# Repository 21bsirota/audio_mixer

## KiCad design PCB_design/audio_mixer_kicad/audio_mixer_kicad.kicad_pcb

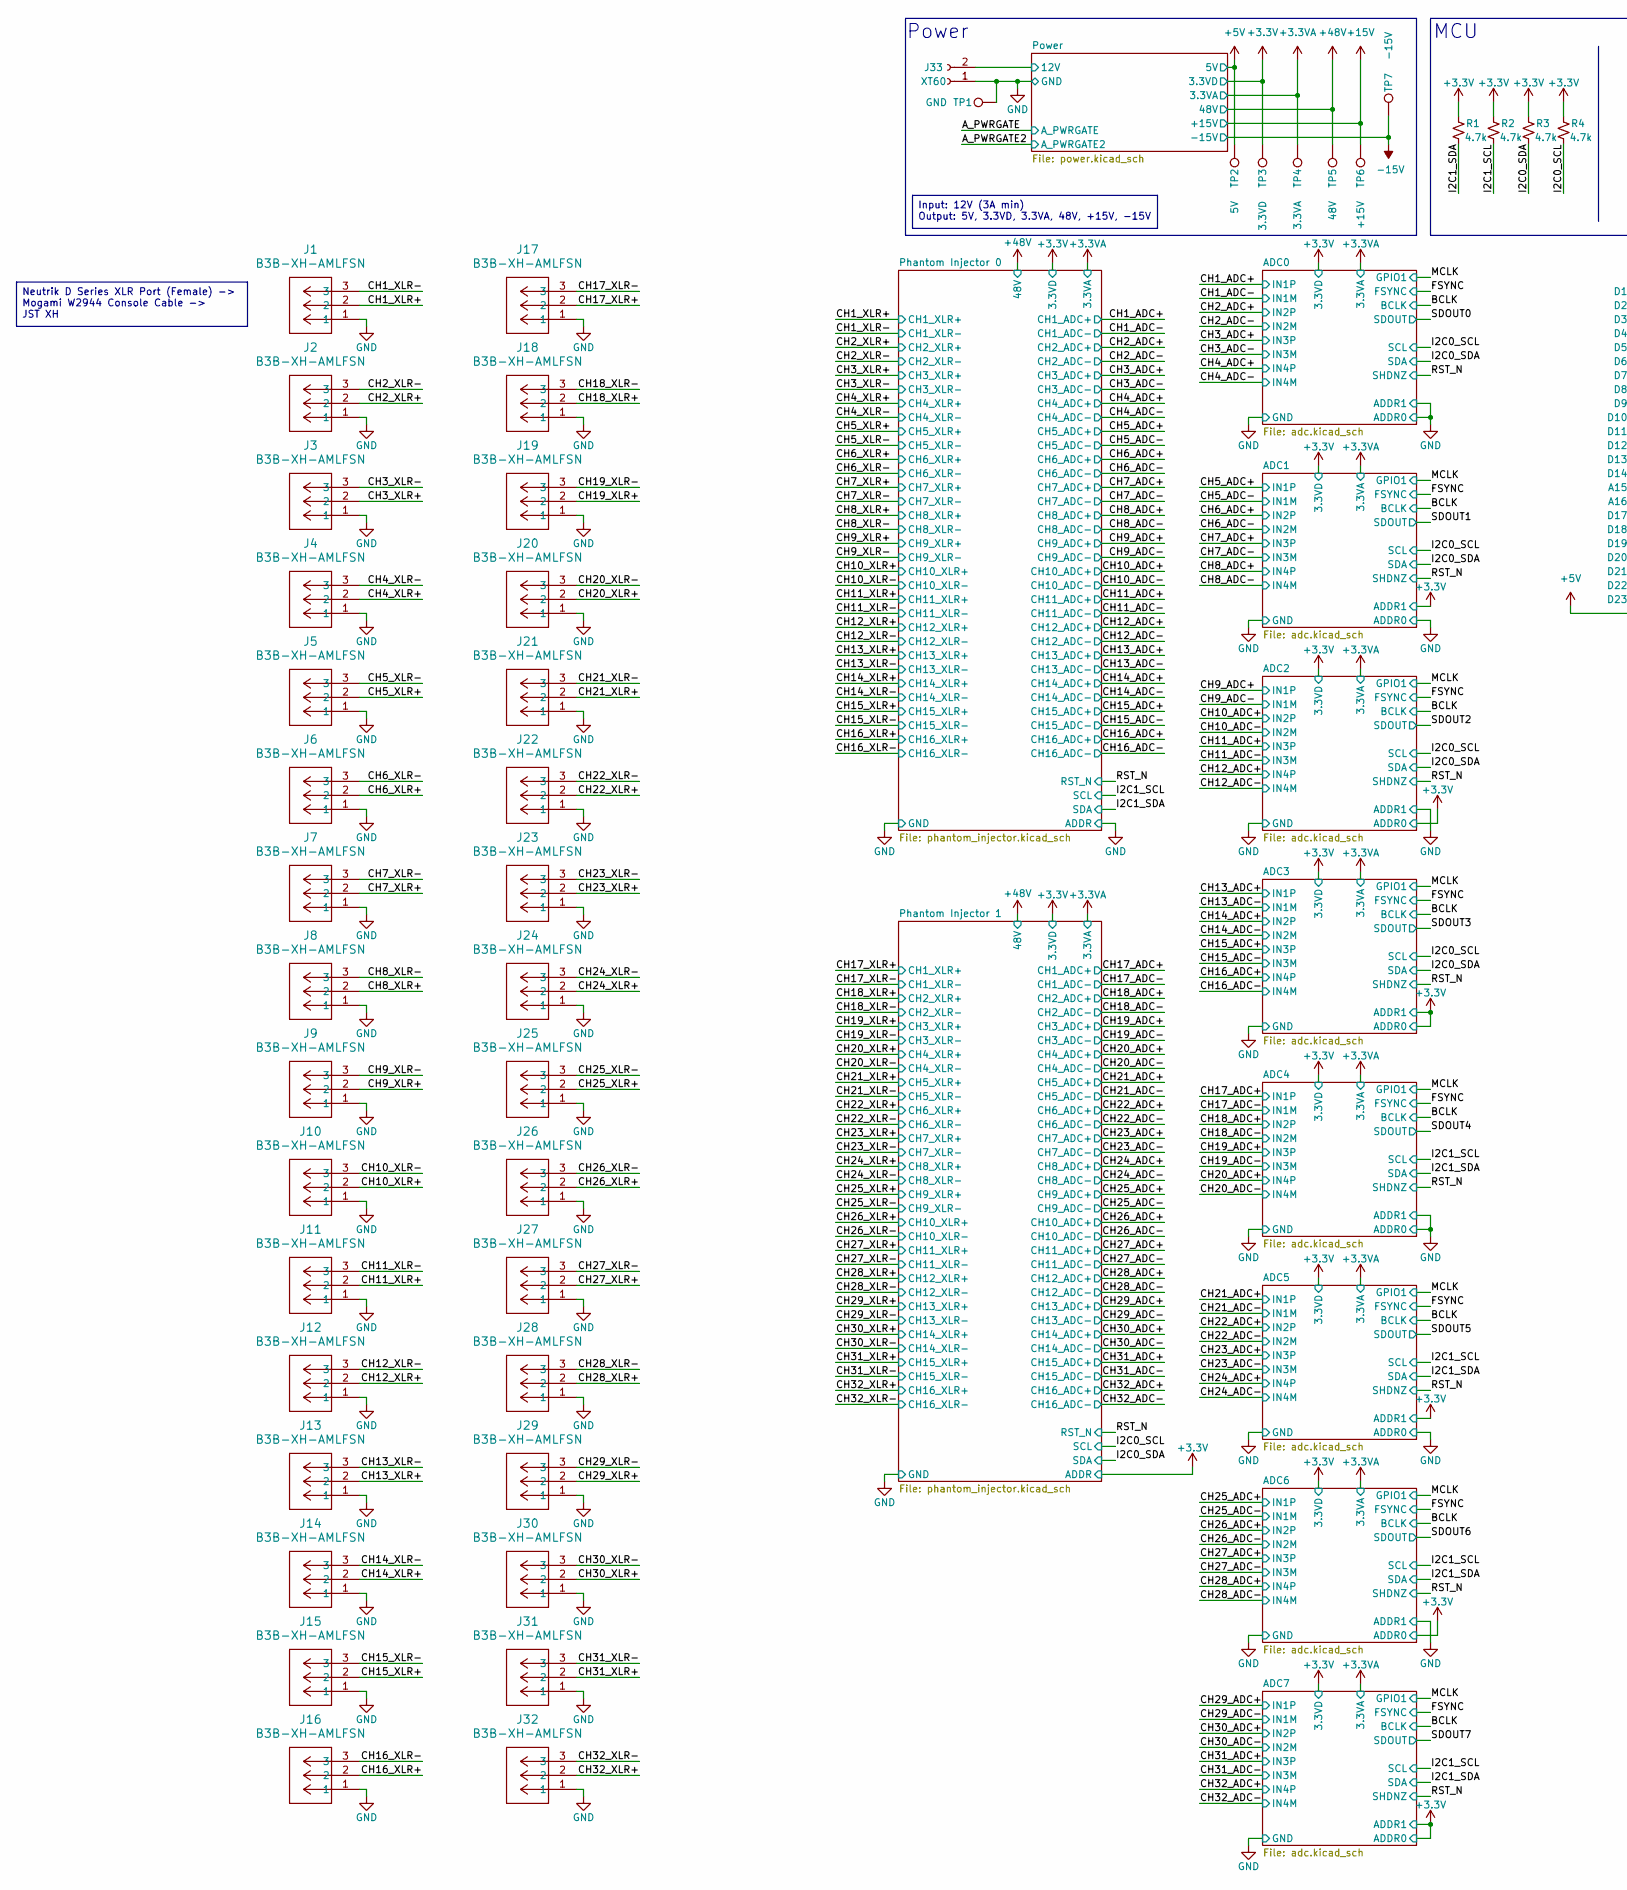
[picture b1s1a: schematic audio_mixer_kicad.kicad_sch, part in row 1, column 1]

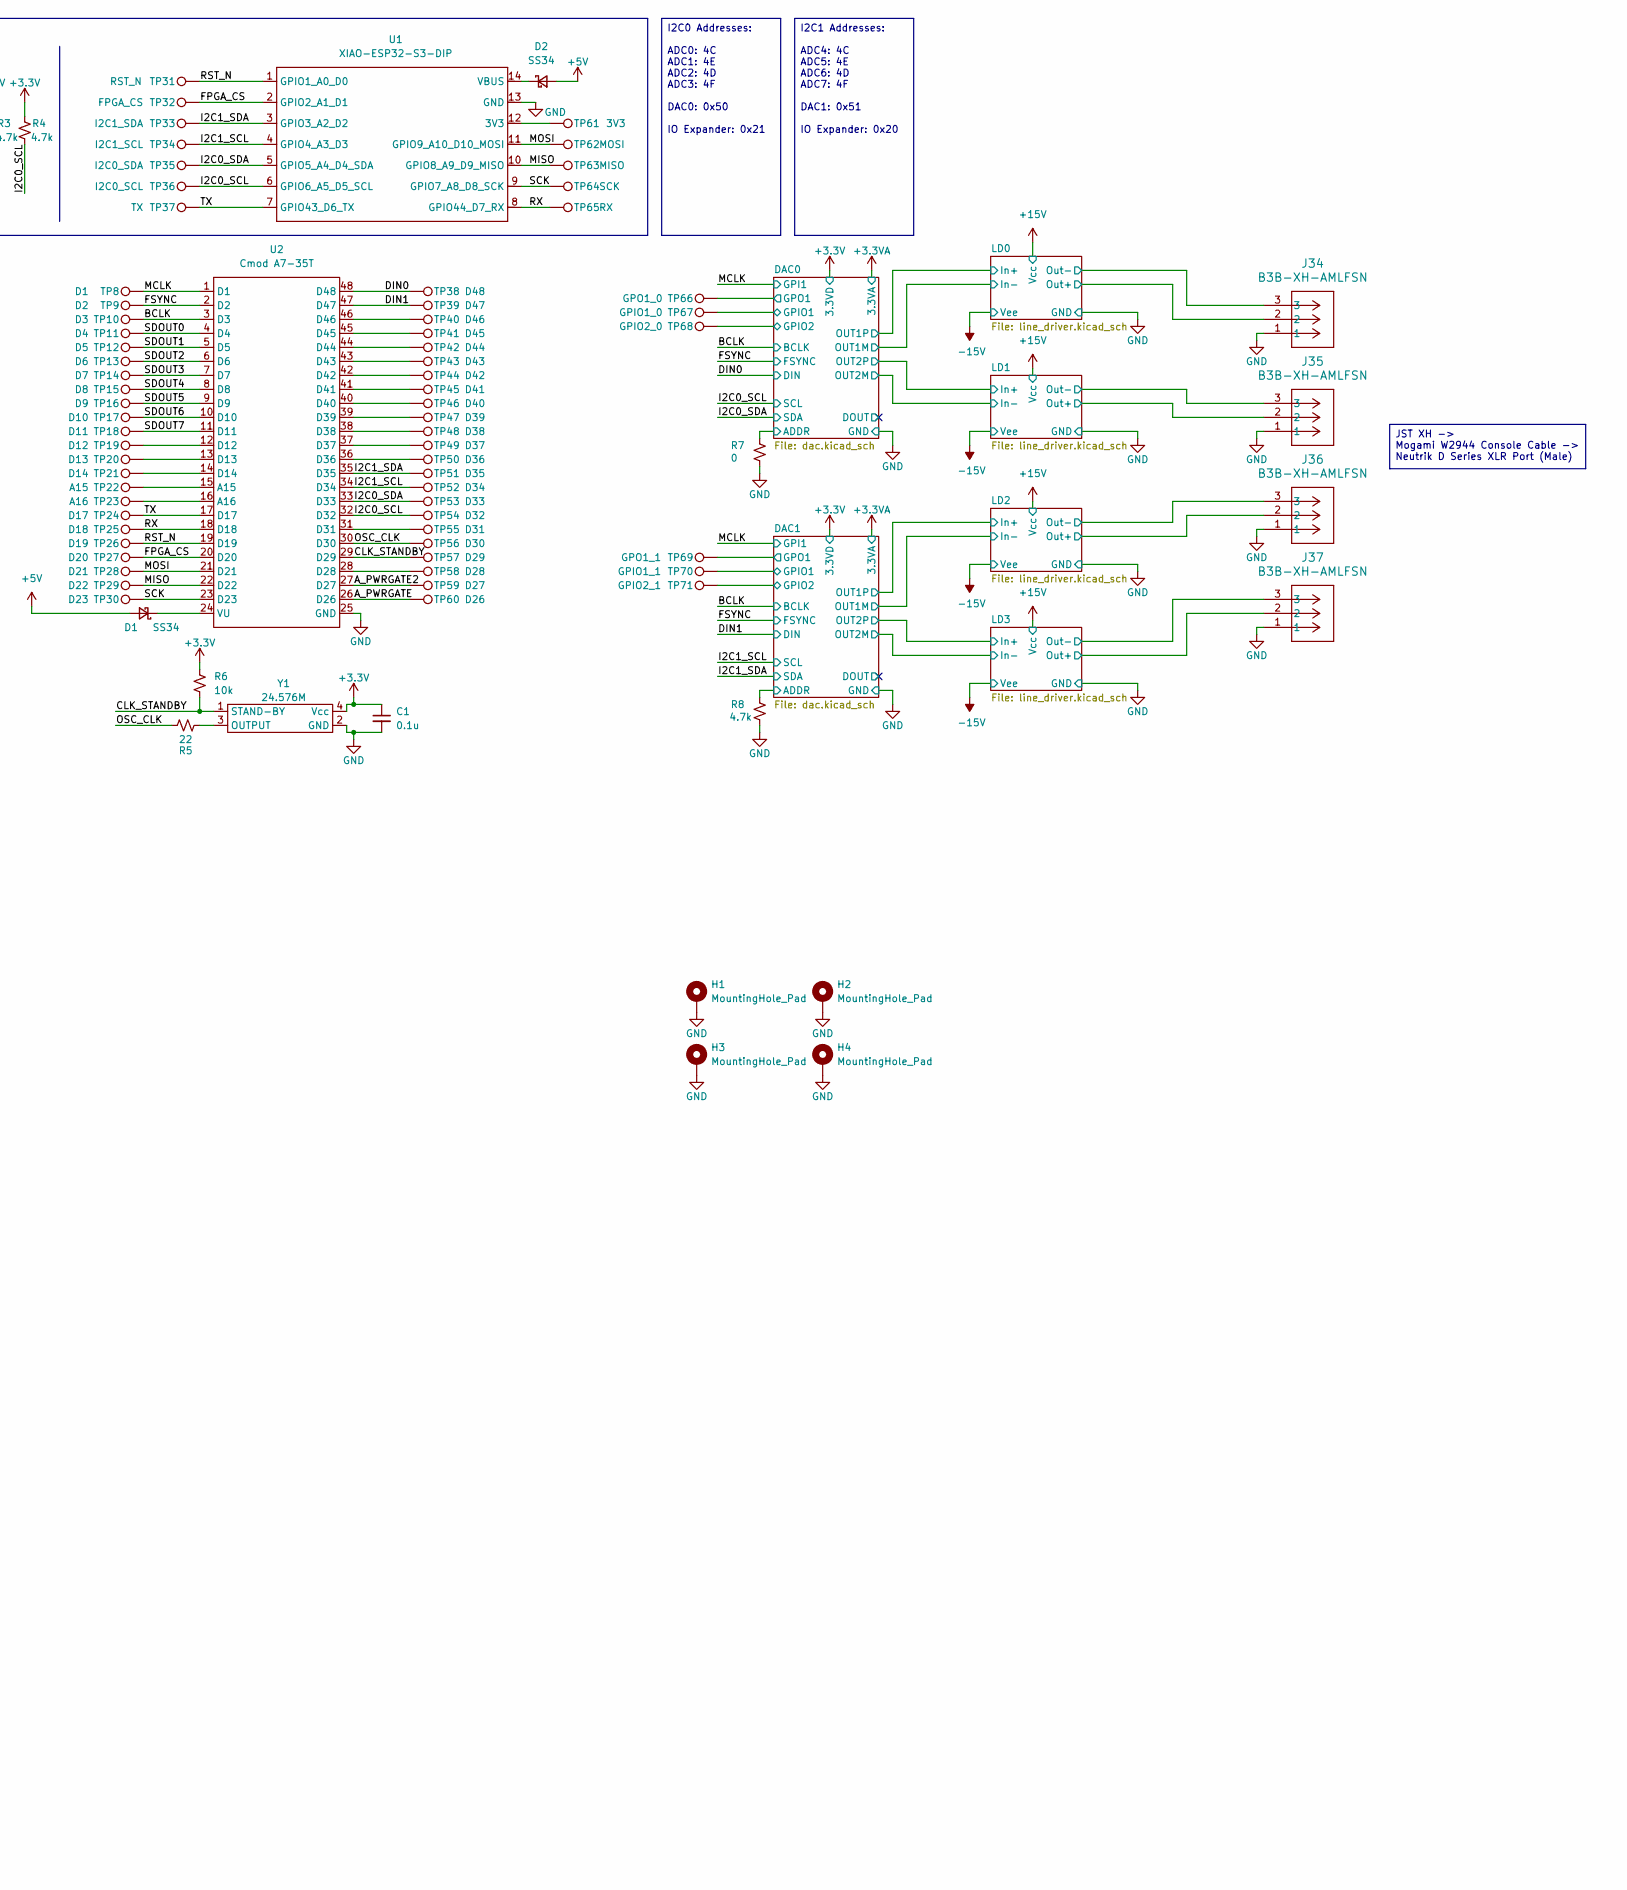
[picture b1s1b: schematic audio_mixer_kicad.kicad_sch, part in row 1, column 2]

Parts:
C1: 0.1u; C_1206_3216Metric_Pad1.33x1.80mm_HandSolder
D1, D2: SS34; DIOM7959X265N
H1, H2, H3, H4: MountingHole_Pad; MountingHole_3.2mm_M3_Pad_TopBottom
J1, J2, J3, J4, J5, J6, J7, J8, J9, J10, J11, J12, J13, J14, J15, J16, J17, J18, J19, J20, J21, J22, J23, J24, J25, J26, J27, J28, J29, J30, J31, J32, J34, J35, J36, J37: B3B-XH-AMLFSN; CONN_B3B-XH-AMLFSN_JST
J33: XT60; AMASS_XT60-M_1x02_P7.20mm_Vertical
R1, R2, R3, R4, R8: 4.7k; R_1206_3216Metric_Pad1.30x1.75mm_HandSolder
R5: 22; R_1206_3216Metric_Pad1.30x1.75mm_HandSolder
R6: 10k; R_1206_3216Metric_Pad1.30x1.75mm_HandSolder
R7: 0; R_1206_3216Metric_Pad1.30x1.75mm_HandSolder
TP1: GND; TestPoint_THTPad_D2.0mm_Drill1.0mm
TP2: 5V; TestPoint_THTPad_D2.0mm_Drill1.0mm
TP3: 3.3VD; TestPoint_THTPad_D2.0mm_Drill1.0mm
TP4: 3.3VA; TestPoint_THTPad_D2.0mm_Drill1.0mm
TP5: 48V; TestPoint_THTPad_D2.0mm_Drill1.0mm
TP6: +15V; TestPoint_THTPad_D2.0mm_Drill1.0mm
TP7: -15V; TestPoint_THTPad_D2.0mm_Drill1.0mm
TP8: D1; TestPoint_THTPad_D2.0mm_Drill1.0mm
TP9: D2; TestPoint_THTPad_D2.0mm_Drill1.0mm
TP10: D3; TestPoint_THTPad_D2.0mm_Drill1.0mm
TP11: D4; TestPoint_THTPad_D2.0mm_Drill1.0mm
TP12: D5; TestPoint_THTPad_D2.0mm_Drill1.0mm
TP13: D6; TestPoint_THTPad_D2.0mm_Drill1.0mm
TP14: D7; TestPoint_THTPad_D2.0mm_Drill1.0mm
TP15: D8; TestPoint_THTPad_D2.0mm_Drill1.0mm
TP16: D9; TestPoint_THTPad_D2.0mm_Drill1.0mm
TP17: D10; TestPoint_THTPad_D2.0mm_Drill1.0mm
TP18: D11; TestPoint_THTPad_D2.0mm_Drill1.0mm
TP19: D12; TestPoint_THTPad_D2.0mm_Drill1.0mm
TP20: D13; TestPoint_THTPad_D2.0mm_Drill1.0mm
TP21: D14; TestPoint_THTPad_D2.0mm_Drill1.0mm
TP22: A15; TestPoint_THTPad_D2.0mm_Drill1.0mm
TP23: A16; TestPoint_THTPad_D2.0mm_Drill1.0mm
TP24: D17; TestPoint_THTPad_D2.0mm_Drill1.0mm
TP25: D18; TestPoint_THTPad_D2.0mm_Drill1.0mm
TP26: D19; TestPoint_THTPad_D2.0mm_Drill1.0mm
TP27: D20; TestPoint_THTPad_D2.0mm_Drill1.0mm
TP28: D21; TestPoint_THTPad_D2.0mm_Drill1.0mm
TP29: D22; TestPoint_THTPad_D2.0mm_Drill1.0mm
TP30: D23; TestPoint_THTPad_D2.0mm_Drill1.0mm
TP31: RST_N; TestPoint_THTPad_D2.0mm_Drill1.0mm
TP32: FPGA_CS; TestPoint_THTPad_D2.0mm_Drill1.0mm
TP33: I2C1_SDA; TestPoint_THTPad_D2.0mm_Drill1.0mm
TP34: I2C1_SCL; TestPoint_THTPad_D2.0mm_Drill1.0mm
TP35: I2C0_SDA; TestPoint_THTPad_D2.0mm_Drill1.0mm
TP36: I2C0_SCL; TestPoint_THTPad_D2.0mm_Drill1.0mm
TP37: TX; TestPoint_THTPad_D2.0mm_Drill1.0mm
TP38: D48; TestPoint_THTPad_D2.0mm_Drill1.0mm
TP39: D47; TestPoint_THTPad_D2.0mm_Drill1.0mm
TP40: D46; TestPoint_THTPad_D2.0mm_Drill1.0mm
TP41: D45; TestPoint_THTPad_D2.0mm_Drill1.0mm
TP42: D44; TestPoint_THTPad_D2.0mm_Drill1.0mm
TP43: D43; TestPoint_THTPad_D2.0mm_Drill1.0mm
TP44: D42; TestPoint_THTPad_D2.0mm_Drill1.0mm
TP45: D41; TestPoint_THTPad_D2.0mm_Drill1.0mm
TP46: D40; TestPoint_THTPad_D2.0mm_Drill1.0mm
TP47: D39; TestPoint_THTPad_D2.0mm_Drill1.0mm
TP48: D38; TestPoint_THTPad_D2.0mm_Drill1.0mm
TP49: D37; TestPoint_THTPad_D2.0mm_Drill1.0mm
TP50: D36; TestPoint_THTPad_D2.0mm_Drill1.0mm
TP51: D35; TestPoint_THTPad_D2.0mm_Drill1.0mm
TP52: D34; TestPoint_THTPad_D2.0mm_Drill1.0mm
TP53: D33; TestPoint_THTPad_D2.0mm_Drill1.0mm
TP54: D32; TestPoint_THTPad_D2.0mm_Drill1.0mm
TP55: D31; TestPoint_THTPad_D2.0mm_Drill1.0mm
TP56: D30; TestPoint_THTPad_D2.0mm_Drill1.0mm
TP57: D29; TestPoint_THTPad_D2.0mm_Drill1.0mm
TP58: D28; TestPoint_THTPad_D2.0mm_Drill1.0mm
TP59: D27; TestPoint_THTPad_D2.0mm_Drill1.0mm
TP60: D26; TestPoint_THTPad_D2.0mm_Drill1.0mm
TP61: 3V3; TestPoint_THTPad_D2.0mm_Drill1.0mm
TP62: MOSI; TestPoint_THTPad_D2.0mm_Drill1.0mm
TP63: MISO; TestPoint_THTPad_D2.0mm_Drill1.0mm
TP64: SCK; TestPoint_THTPad_D2.0mm_Drill1.0mm
TP65: RX; TestPoint_THTPad_D2.0mm_Drill1.0mm
TP66: GPO1_0; TestPoint_THTPad_D2.0mm_Drill1.0mm
TP67: GPIO1_0; TestPoint_THTPad_D2.0mm_Drill1.0mm
TP68: GPIO2_0; TestPoint_THTPad_D2.0mm_Drill1.0mm
TP69: GPO1_1; TestPoint_THTPad_D2.0mm_Drill1.0mm
TP70: GPIO1_1; TestPoint_THTPad_D2.0mm_Drill1.0mm
TP71: GPIO2_1; TestPoint_THTPad_D2.0mm_Drill1.0mm
U1: XIAO-ESP32-S3-DIP
U2: Cmod A7-35T; Cmod-A7
Y1: 24.576M; NZ2520SDA

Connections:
+3.3V: C1.1, R1.1, R2.1, R3.1, R4.1, R6.1, TP3.1 (1_1), Y1.4 (Vcc); also elsewhere on the board
+3.3VA: TP4.1 (1_1); also elsewhere on the board
+5V: D1.2 (A), D2.2 (A), TP2.1 (1_1); also elsewhere on the board
+12V: J33.2; also elsewhere on the board
+15V: TP6.1 (1_1); also elsewhere on the board
+48V: TP5.1 (1_1); also elsewhere on the board
-15V: TP7.1 (1_1); also elsewhere on the board
/A_PWRGATE: TP60.1 (1_1), U2.26 (D26); also elsewhere on the board
/A_PWRGATE2: TP59.1 (1_1), U2.27 (D27); also elsewhere on the board
/BCLK: TP10.1 (1_1), U2.3 (D3); also elsewhere on the board
/CH1_XLR+: J1.2; also elsewhere on the board
/CH1_XLR-: J1.3; also elsewhere on the board
/CH2_XLR+: J2.2; also elsewhere on the board
/CH2_XLR-: J2.3; also elsewhere on the board
/CH3_XLR+: J3.2; also elsewhere on the board
/CH3_XLR-: J3.3; also elsewhere on the board
/CH4_XLR+: J4.2; also elsewhere on the board
/CH4_XLR-: J4.3; also elsewhere on the board
/CH5_XLR+: J5.2; also elsewhere on the board
/CH5_XLR-: J5.3; also elsewhere on the board
/CH6_XLR+: J6.2; also elsewhere on the board
/CH6_XLR-: J6.3; also elsewhere on the board
/CH7_XLR+: J7.2; also elsewhere on the board
/CH7_XLR-: J7.3; also elsewhere on the board
/CH8_XLR+: J8.2; also elsewhere on the board
/CH8_XLR-: J8.3; also elsewhere on the board
/CH9_XLR+: J9.2; also elsewhere on the board
/CH9_XLR-: J9.3; also elsewhere on the board
/CH10_XLR+: J10.2; also elsewhere on the board
/CH10_XLR-: J10.3; also elsewhere on the board
/CH11_XLR+: J11.2; also elsewhere on the board
/CH11_XLR-: J11.3; also elsewhere on the board
/CH12_XLR+: J12.2; also elsewhere on the board
/CH12_XLR-: J12.3; also elsewhere on the board
/CH13_XLR+: J13.2; also elsewhere on the board
/CH13_XLR-: J13.3; also elsewhere on the board
/CH14_XLR+: J14.2; also elsewhere on the board
/CH14_XLR-: J14.3; also elsewhere on the board
/CH15_XLR+: J15.2; also elsewhere on the board
/CH15_XLR-: J15.3; also elsewhere on the board
/CH16_XLR+: J16.2; also elsewhere on the board
/CH16_XLR-: J16.3; also elsewhere on the board
/CH17_XLR+: J17.2; also elsewhere on the board
/CH17_XLR-: J17.3; also elsewhere on the board
/CH18_XLR+: J18.2; also elsewhere on the board
/CH18_XLR-: J18.3; also elsewhere on the board
/CH19_XLR+: J19.2; also elsewhere on the board
/CH19_XLR-: J19.3; also elsewhere on the board
/CH20_XLR+: J20.2; also elsewhere on the board
/CH20_XLR-: J20.3; also elsewhere on the board
/CH21_XLR+: J21.2; also elsewhere on the board
/CH21_XLR-: J21.3; also elsewhere on the board
/CH22_XLR+: J22.2; also elsewhere on the board
/CH22_XLR-: J22.3; also elsewhere on the board
/CH23_XLR+: J23.2; also elsewhere on the board
/CH23_XLR-: J23.3; also elsewhere on the board
/CH24_XLR+: J24.2; also elsewhere on the board
/CH24_XLR-: J24.3; also elsewhere on the board
/CH25_XLR+: J25.2; also elsewhere on the board
/CH25_XLR-: J25.3; also elsewhere on the board
/CH26_XLR+: J26.2; also elsewhere on the board
/CH26_XLR-: J26.3; also elsewhere on the board
/CH27_XLR+: J27.2; also elsewhere on the board
/CH27_XLR-: J27.3; also elsewhere on the board
/CH28_XLR+: J28.2; also elsewhere on the board
/CH28_XLR-: J28.3; also elsewhere on the board
/CH29_XLR+: J29.2; also elsewhere on the board
/CH29_XLR-: J29.3; also elsewhere on the board
/CH30_XLR+: J30.2; also elsewhere on the board
/CH30_XLR-: J30.3; also elsewhere on the board
/CH31_XLR+: J31.2; also elsewhere on the board
/CH31_XLR-: J31.3; also elsewhere on the board
/CH32_XLR+: J32.2; also elsewhere on the board
/CH32_XLR-: J32.3; also elsewhere on the board
/CLK_STANDBY: R6.2, TP57.1 (1_1), U2.29 (D29), Y1.1 (STAND-BY)
/DAC0/ADDR: R7.1; also elsewhere on the board
/DAC0/GPIO1: TP67.1 (1_1); also elsewhere on the board
/DAC0/GPIO2: TP68.1 (1_1); also elsewhere on the board
/DAC0/GPO1: TP66.1 (1_1); also elsewhere on the board
/DAC1/ADDR: R8.1; also elsewhere on the board
/DAC1/GPIO1: TP70.1 (1_1); also elsewhere on the board
/DAC1/GPIO2: TP71.1 (1_1); also elsewhere on the board
/DAC1/GPO1: TP69.1 (1_1); also elsewhere on the board
/DIN0: TP38.1 (1_1), U2.48 (D48); also elsewhere on the board
/DIN1: TP39.1 (1_1), U2.47 (D47); also elsewhere on the board
/FPGA_CS: TP27.1 (1_1), TP32.1 (1_1), U1.2 (GPIO2_A1_D1), U2.20 (D20)
/FSYNC: TP9.1 (1_1), U2.2 (D2); also elsewhere on the board
/I2C0_SCL: R4.2, TP36.1 (1_1), TP54.1 (1_1), U1.6 (GPIO6_A5_D5_SCL), U2.32 (D32); also elsewhere on the board
/I2C0_SDA: R3.2, TP35.1 (1_1), TP53.1 (1_1), U1.5 (GPIO5_A4_D4_SDA), U2.33 (D33); also elsewhere on the board
/I2C1_SCL: R2.2, TP34.1 (1_1), TP52.1 (1_1), U1.4 (GPIO4_A3_D3), U2.34 (D34); also elsewhere on the board
/I2C1_SDA: R1.2, TP33.1 (1_1), TP51.1 (1_1), U1.3 (GPIO3_A2_D2), U2.35 (D35); also elsewhere on the board
/LD0/Out+: J34.2; also elsewhere on the board
/LD0/Out-: J34.3; also elsewhere on the board
/LD1/Out+: J35.2; also elsewhere on the board
/LD1/Out-: J35.3; also elsewhere on the board
/LD2/Out+: J36.2; also elsewhere on the board
/LD2/Out-: J36.3; also elsewhere on the board
/LD3/Out+: J37.2; also elsewhere on the board
/LD3/Out-: J37.3; also elsewhere on the board
/MCLK: TP8.1 (1_1), U2.1 (D1); also elsewhere on the board
/MISO: TP29.1 (1_1), TP63.1 (1_1), U1.10 (GPIO8_A9_D9_MISO), U2.22 (D22)
/MOSI: TP28.1 (1_1), TP62.1 (1_1), U1.11 (GPIO9_A10_D10_MOSI), U2.21 (D21)
/OSC_CLK: R5.1, TP56.1 (1_1), U2.30 (D30)
/RST_N: TP26.1 (1_1), TP31.1 (1_1), U1.1 (GPIO1_A0_D0), U2.19 (D19); also elsewhere on the board
/RX: TP25.1 (1_1), TP65.1 (1_1), U1.8 (GPIO44_D7_RX), U2.18 (D18)
/SCK: TP30.1 (1_1), TP64.1 (1_1), U1.9 (GPIO7_A8_D8_SCK), U2.23 (D23)
/SDOUT0: TP11.1 (1_1), U2.4 (D4); also elsewhere on the board
/SDOUT1: TP12.1 (1_1), U2.5 (D5); also elsewhere on the board
/SDOUT2: TP13.1 (1_1), U2.6 (D6); also elsewhere on the board
/SDOUT3: TP14.1 (1_1), U2.7 (D7); also elsewhere on the board
/SDOUT4: TP15.1 (1_1), U2.8 (D8); also elsewhere on the board
/SDOUT5: TP16.1 (1_1), U2.9 (D9); also elsewhere on the board
/SDOUT6: TP17.1 (1_1), U2.10 (D10); also elsewhere on the board
/SDOUT7: TP18.1 (1_1), U2.11 (D11); also elsewhere on the board
/TX: TP24.1 (1_1), TP37.1 (1_1), U1.7 (GPIO43_D6_TX), U2.17 (D17)
GND: C1.2, H1.1 (1_1), H2.1 (1_1), H3.1 (1_1), H4.1 (1_1), J1.1, J2.1, J3.1, J4.1, J5.1, J6.1, J7.1, J8.1, J9.1, J10.1, J11.1, J12.1, J13.1, J14.1, J15.1, J16.1, J17.1, J18.1, J19.1, J20.1, J21.1, J22.1, J23.1, J24.1, J25.1, J26.1, J27.1, J28.1, J29.1, J30.1, J31.1, J32.1, J33.1, J34.1, J35.1, J36.1, J37.1, R7.2, R8.2, TP1.1 (1_1), U1.13 (GND), U2.25 (GND), Y1.2 (GND); also elsewhere on the board
unnamed: D1.1 (K), U2.24 (VU)
unnamed: D2.1 (K), U1.14 (VBUS)
unnamed: TP61.1 (1_1), U1.12 (3V3)
unnamed: TP22.1 (1_1), U2.15 (A15)
unnamed: TP23.1 (1_1), U2.16 (A16)
unnamed: TP19.1 (1_1), U2.12 (D12)
unnamed: TP20.1 (1_1), U2.13 (D13)
unnamed: TP21.1 (1_1), U2.14 (D14)
unnamed: TP58.1 (1_1), U2.28 (D28)
unnamed: TP55.1 (1_1), U2.31 (D31)
unnamed: TP50.1 (1_1), U2.36 (D36)
unnamed: TP49.1 (1_1), U2.37 (D37)
unnamed: TP48.1 (1_1), U2.38 (D38)
unnamed: TP47.1 (1_1), U2.39 (D39)
unnamed: TP46.1 (1_1), U2.40 (D40)
unnamed: TP45.1 (1_1), U2.41 (D41)
unnamed: TP44.1 (1_1), U2.42 (D42)
unnamed: TP43.1 (1_1), U2.43 (D43)
unnamed: TP42.1 (1_1), U2.44 (D44)
unnamed: TP41.1 (1_1), U2.45 (D45)
unnamed: TP40.1 (1_1), U2.46 (D46)
unnamed: R5.2, Y1.3 (OUTPUT)

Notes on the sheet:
MCU
Power
JST XH -> Mogami W2944 Console Cable -> Neutrik D Series XLR Port (Male)
Neutrik D Series XLR Port (Female) -> Mogami W2944 Console Cable -> JST XH
I2C1 Addresses: ADC4: 4C ADC5: 4E ADC6: 4D ADC7: 4F DAC1: 0x51 IO Expander: 0x20
I2C0 Addresses: ADC0: 4C ADC1: 4E ADC2: 4D ADC3: 4F DAC0: 0x50 IO Expander: 0x21
Input: 12V (3A min) Output: 5V, 3.3VD, 3.3VA, 48V, +15V, -15V

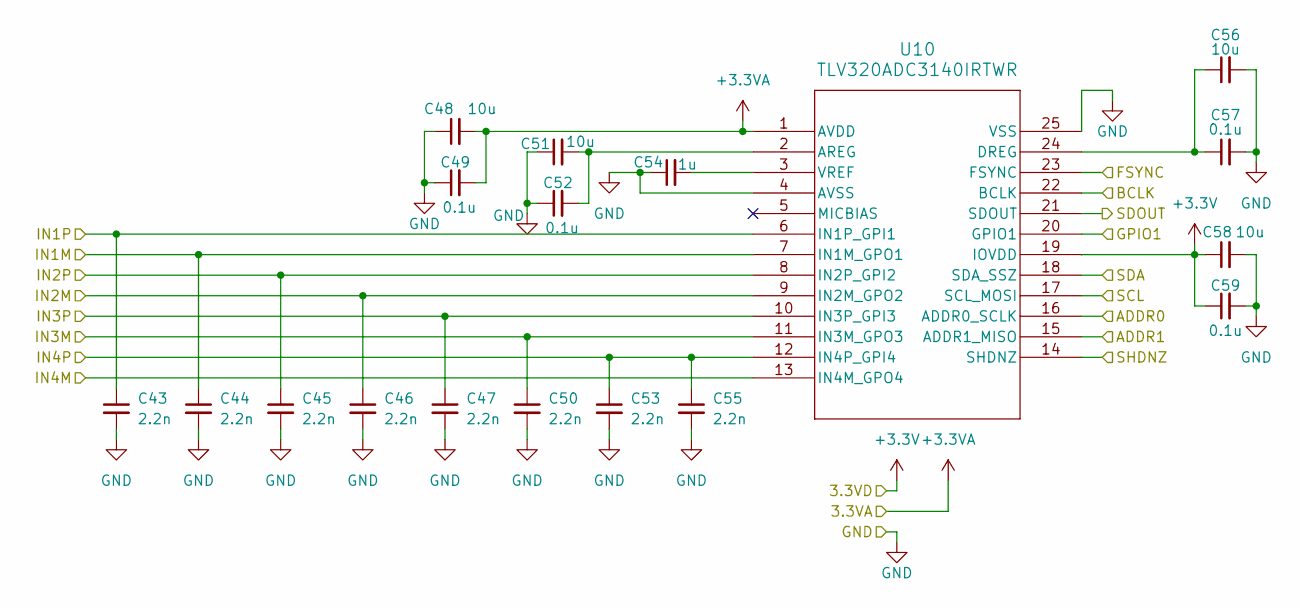
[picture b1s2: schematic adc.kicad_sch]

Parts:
C43, C44, C45, C46, C47, C50, C53, C55: 2.2n; C_1206_3216Metric_Pad1.33x1.80mm_HandSolder
C48, C51, C56, C58: 10u; C_1206_3216Metric_Pad1.33x1.80mm_HandSolder
C49, C52, C57, C59: 0.1u; C_1206_3216Metric_Pad1.33x1.80mm_HandSolder
C54: 1u; C_1206_3216Metric_Pad1.33x1.80mm_HandSolder
U10: TLV320ADC3140IRTWR; TLV320ADC3140IRTWR_TEX

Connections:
+3.3V: C58.1, C59.1, U10.19 (IOVDD); also elsewhere on the board
+3.3VA: C48.2, C49.2, U10.1 (AVDD); also elsewhere on the board
/BCLK: U10.22 (BCLK); also elsewhere on the board
/CH1_ADC+: C43.1, U10.6 (IN1P_GPI1); also elsewhere on the board
/CH1_ADC-: C44.1, U10.7 (IN1M_GPO1); also elsewhere on the board
/CH2_ADC+: C45.1, U10.8 (IN2P_GPI2); also elsewhere on the board
/CH2_ADC-: C46.1, U10.9 (IN2M_GPO2); also elsewhere on the board
/CH3_ADC+: C47.1, U10.10 (IN3P_GPI3); also elsewhere on the board
/CH3_ADC-: C50.1, U10.11 (IN3M_GPO3); also elsewhere on the board
/CH4_ADC+: C53.1, C55.1, U10.12 (IN4P_GPI4); also elsewhere on the board
/CH4_ADC-: U10.13 (IN4M_GPO4); also elsewhere on the board
/FSYNC: U10.23 (FSYNC); also elsewhere on the board
/I2C0_SCL: U10.17 (SCL_MOSI); also elsewhere on the board
/I2C0_SDA: U10.18 (SDA_SSZ); also elsewhere on the board
/MCLK: U10.20 (GPIO1); also elsewhere on the board
/RST_N: U10.14 (SHDNZ); also elsewhere on the board
/SDOUT0: U10.21 (SDOUT); also elsewhere on the board
GND: C43.2, C44.2, C45.2, C46.2, C47.2, C48.1, C49.1, C50.2, C51.1, C52.1, C53.2, C54.1, C55.2, C56.2, C57.2, C58.2, C59.2, U10.4 (AVSS), U10.15 (ADDR1_MISO), U10.16 (ADDR0_SCLK), U10.25 (VSS); also elsewhere on the board
unnamed: C51.2, C52.2, U10.2 (AREG)
unnamed: C56.1, C57.1, U10.24 (DREG)
unnamed: C54.2, U10.3 (VREF)

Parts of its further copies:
C60, C61, C62, C63, C64, C67, C70, C72, C77, C78, C79, C80, C81, C84, C87, C89, C94, C95, C96, C97, C98, C101, C104, C106, C111, C112, C113, C114, C115, C118, C121, C123, C128, C129, C130, C131, C132, C135, C138, C140, C145, C146, C147, C148, C149, C152, C155, C157, C162, C163, C164, C165, C166, C169, C172, C174: 2.2n; C_1206_3216Metric_Pad1.33x1.80mm_HandSolder
C65, C68, C73, C75, C82, C85, C90, C92, C99, C102, C107, C109, C116, C119, C124, C126, C133, C136, C141, C143, C150, C153, C158, C160, C167, C170, C175, C177: 10u; C_1206_3216Metric_Pad1.33x1.80mm_HandSolder
C66, C69, C74, C76, C83, C86, C91, C93, C100, C103, C108, C110, C117, C120, C125, C127, C134, C137, C142, C144, C151, C154, C159, C161, C168, C171, C176, C178: 0.1u; C_1206_3216Metric_Pad1.33x1.80mm_HandSolder
C71, C88, C105, C122, C139, C156, C173: 1u; C_1206_3216Metric_Pad1.33x1.80mm_HandSolder
U11, U12, U13, U14, U15, U16, U17: TLV320ADC3140IRTWR; TLV320ADC3140IRTWR_TEX

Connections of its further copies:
+3.3V: C75.1, C76.1, C92.1, C93.1, C109.1, C110.1, C126.1, C127.1, C143.1, C144.1, C160.1, C161.1, C177.1, C178.1, U11.15 (ADDR1_MISO), U11.19 (IOVDD), U12.16 (ADDR0_SCLK), U12.19 (IOVDD), U13.15 (ADDR1_MISO), U13.16 (ADDR0_SCLK), U13.19 (IOVDD), U14.19 (IOVDD), U15.15 (ADDR1_MISO), U15.19 (IOVDD), U16.16 (ADDR0_SCLK), U16.19 (IOVDD), U17.15 (ADDR1_MISO), U17.16 (ADDR0_SCLK), U17.19 (IOVDD); also elsewhere on the board
+3.3VA: C65.2, C66.2, C82.2, C83.2, C99.2, C100.2, C116.2, C117.2, C133.2, C134.2, C150.2, C151.2, C167.2, C168.2, U11.1 (AVDD), U12.1 (AVDD), U13.1 (AVDD), U14.1 (AVDD), U15.1 (AVDD), U16.1 (AVDD), U17.1 (AVDD); also elsewhere on the board
/BCLK: U11.22 (BCLK), U12.22 (BCLK), U13.22 (BCLK), U14.22 (BCLK), U15.22 (BCLK), U16.22 (BCLK), U17.22 (BCLK); also elsewhere on the board
/CH5_ADC+: C60.1, U11.6 (IN1P_GPI1); also elsewhere on the board
/CH5_ADC-: C61.1, U11.7 (IN1M_GPO1); also elsewhere on the board
/CH6_ADC+: C62.1, U11.8 (IN2P_GPI2); also elsewhere on the board
/CH6_ADC-: C63.1, U11.9 (IN2M_GPO2); also elsewhere on the board
/CH7_ADC+: C64.1, U11.10 (IN3P_GPI3); also elsewhere on the board
/CH7_ADC-: C67.1, U11.11 (IN3M_GPO3); also elsewhere on the board
/CH8_ADC+: C70.1, C72.1, U11.12 (IN4P_GPI4); also elsewhere on the board
/CH8_ADC-: U11.13 (IN4M_GPO4); also elsewhere on the board
/CH9_ADC+: C77.1, U12.6 (IN1P_GPI1); also elsewhere on the board
/CH9_ADC-: C78.1, U12.7 (IN1M_GPO1); also elsewhere on the board
/CH10_ADC+: C79.1, U12.8 (IN2P_GPI2); also elsewhere on the board
/CH10_ADC-: C80.1, U12.9 (IN2M_GPO2); also elsewhere on the board
/CH11_ADC+: C81.1, U12.10 (IN3P_GPI3); also elsewhere on the board
/CH11_ADC-: C84.1, U12.11 (IN3M_GPO3); also elsewhere on the board
/CH12_ADC+: C87.1, C89.1, U12.12 (IN4P_GPI4); also elsewhere on the board
/CH12_ADC-: U12.13 (IN4M_GPO4); also elsewhere on the board
/CH13_ADC+: C94.1, U13.6 (IN1P_GPI1); also elsewhere on the board
/CH13_ADC-: C95.1, U13.7 (IN1M_GPO1); also elsewhere on the board
/CH14_ADC+: C96.1, U13.8 (IN2P_GPI2); also elsewhere on the board
/CH14_ADC-: C97.1, U13.9 (IN2M_GPO2); also elsewhere on the board
/CH15_ADC+: C98.1, U13.10 (IN3P_GPI3); also elsewhere on the board
/CH15_ADC-: C101.1, U13.11 (IN3M_GPO3); also elsewhere on the board
/CH16_ADC+: C104.1, C106.1, U13.12 (IN4P_GPI4); also elsewhere on the board
/CH16_ADC-: U13.13 (IN4M_GPO4); also elsewhere on the board
/CH17_ADC+: C111.1, U14.6 (IN1P_GPI1); also elsewhere on the board
/CH17_ADC-: C112.1, U14.7 (IN1M_GPO1); also elsewhere on the board
/CH18_ADC+: C113.1, U14.8 (IN2P_GPI2); also elsewhere on the board
/CH18_ADC-: C114.1, U14.9 (IN2M_GPO2); also elsewhere on the board
/CH19_ADC+: C115.1, U14.10 (IN3P_GPI3); also elsewhere on the board
/CH19_ADC-: C118.1, U14.11 (IN3M_GPO3); also elsewhere on the board
/CH20_ADC+: C121.1, C123.1, U14.12 (IN4P_GPI4); also elsewhere on the board
/CH20_ADC-: U14.13 (IN4M_GPO4); also elsewhere on the board
/CH21_ADC+: C128.1, U15.6 (IN1P_GPI1); also elsewhere on the board
/CH21_ADC-: C129.1, U15.7 (IN1M_GPO1); also elsewhere on the board
/CH22_ADC+: C130.1, U15.8 (IN2P_GPI2); also elsewhere on the board
/CH22_ADC-: C131.1, U15.9 (IN2M_GPO2); also elsewhere on the board
/CH23_ADC+: C132.1, U15.10 (IN3P_GPI3); also elsewhere on the board
/CH23_ADC-: C135.1, U15.11 (IN3M_GPO3); also elsewhere on the board
/CH24_ADC+: C138.1, C140.1, U15.12 (IN4P_GPI4); also elsewhere on the board
/CH24_ADC-: U15.13 (IN4M_GPO4); also elsewhere on the board
/CH25_ADC+: C145.1, U16.6 (IN1P_GPI1); also elsewhere on the board
/CH25_ADC-: C146.1, U16.7 (IN1M_GPO1); also elsewhere on the board
/CH26_ADC+: C147.1, U16.8 (IN2P_GPI2); also elsewhere on the board
/CH26_ADC-: C148.1, U16.9 (IN2M_GPO2); also elsewhere on the board
/CH27_ADC+: C149.1, U16.10 (IN3P_GPI3); also elsewhere on the board
/CH27_ADC-: C152.1, U16.11 (IN3M_GPO3); also elsewhere on the board
/CH28_ADC+: C155.1, C157.1, U16.12 (IN4P_GPI4); also elsewhere on the board
/CH28_ADC-: U16.13 (IN4M_GPO4); also elsewhere on the board
/CH29_ADC+: C162.1, U17.6 (IN1P_GPI1); also elsewhere on the board
/CH29_ADC-: C163.1, U17.7 (IN1M_GPO1); also elsewhere on the board
/CH30_ADC+: C164.1, U17.8 (IN2P_GPI2); also elsewhere on the board
/CH30_ADC-: C165.1, U17.9 (IN2M_GPO2); also elsewhere on the board
/CH31_ADC+: C166.1, U17.10 (IN3P_GPI3); also elsewhere on the board
/CH31_ADC-: C169.1, U17.11 (IN3M_GPO3); also elsewhere on the board
/CH32_ADC+: C172.1, C174.1, U17.12 (IN4P_GPI4); also elsewhere on the board
/CH32_ADC-: U17.13 (IN4M_GPO4); also elsewhere on the board
/FSYNC: U11.23 (FSYNC), U12.23 (FSYNC), U13.23 (FSYNC), U14.23 (FSYNC), U15.23 (FSYNC), U16.23 (FSYNC), U17.23 (FSYNC); also elsewhere on the board
/I2C0_SCL: U11.17 (SCL_MOSI), U12.17 (SCL_MOSI), U13.17 (SCL_MOSI); also elsewhere on the board
/I2C0_SDA: U11.18 (SDA_SSZ), U12.18 (SDA_SSZ), U13.18 (SDA_SSZ); also elsewhere on the board
/I2C1_SCL: U14.17 (SCL_MOSI), U15.17 (SCL_MOSI), U16.17 (SCL_MOSI), U17.17 (SCL_MOSI); also elsewhere on the board
/I2C1_SDA: U14.18 (SDA_SSZ), U15.18 (SDA_SSZ), U16.18 (SDA_SSZ), U17.18 (SDA_SSZ); also elsewhere on the board
/MCLK: U11.20 (GPIO1), U12.20 (GPIO1), U13.20 (GPIO1), U14.20 (GPIO1), U15.20 (GPIO1), U16.20 (GPIO1), U17.20 (GPIO1); also elsewhere on the board
/RST_N: U11.14 (SHDNZ), U12.14 (SHDNZ), U13.14 (SHDNZ), U14.14 (SHDNZ), U15.14 (SHDNZ), U16.14 (SHDNZ), U17.14 (SHDNZ); also elsewhere on the board
/SDOUT1: U11.21 (SDOUT); also elsewhere on the board
/SDOUT2: U12.21 (SDOUT); also elsewhere on the board
/SDOUT3: U13.21 (SDOUT); also elsewhere on the board
/SDOUT4: U14.21 (SDOUT); also elsewhere on the board
/SDOUT5: U15.21 (SDOUT); also elsewhere on the board
/SDOUT6: U16.21 (SDOUT); also elsewhere on the board
/SDOUT7: U17.21 (SDOUT); also elsewhere on the board
GND: C60.2, C61.2, C62.2, C63.2, C64.2, C65.1, C66.1, C67.2, C68.1, C69.1, C70.2, C71.1, C72.2, C73.2, C74.2, C75.2, C76.2, C77.2, C78.2, C79.2, C80.2, C81.2, C82.1, C83.1, C84.2, C85.1, C86.1, C87.2, C88.1, C89.2, C90.2, C91.2, C92.2, C93.2, C94.2, C95.2, C96.2, C97.2, C98.2, C99.1, C100.1, C101.2, C102.1, C103.1, C104.2, C105.1, C106.2, C107.2, C108.2, C109.2, C110.2, C111.2, C112.2, C113.2, C114.2, C115.2, C116.1, C117.1, C118.2, C119.1, C120.1, C121.2, C122.1, C123.2, C124.2, C125.2, C126.2, C127.2, C128.2, C129.2, C130.2, C131.2, C132.2, C133.1, C134.1, C135.2, C136.1, C137.1, C138.2, C139.1, C140.2, C141.2, C142.2, C143.2, C144.2, C145.2, C146.2, C147.2, C148.2, C149.2, C150.1, C151.1, C152.2, C153.1, C154.1, C155.2, C156.1, C157.2, C158.2, C159.2, C160.2, C161.2, C162.2, C163.2, C164.2, C165.2, C166.2, C167.1, C168.1, C169.2, C170.1, C171.1, C172.2, C173.1, C174.2, C175.2, C176.2, C177.2, C178.2, U11.4 (AVSS), U11.16 (ADDR0_SCLK), U11.25 (VSS), U12.4 (AVSS), U12.15 (ADDR1_MISO), U12.25 (VSS), U13.4 (AVSS), U13.25 (VSS), U14.4 (AVSS), U14.15 (ADDR1_MISO), U14.16 (ADDR0_SCLK), U14.25 (VSS), U15.4 (AVSS), U15.16 (ADDR0_SCLK), U15.25 (VSS), U16.4 (AVSS), U16.15 (ADDR1_MISO), U16.25 (VSS), U17.4 (AVSS), U17.25 (VSS); also elsewhere on the board
unnamed: C68.2, C69.2, U11.2 (AREG)
unnamed: C73.1, C74.1, U11.24 (DREG)
unnamed: C71.2, U11.3 (VREF)
unnamed: C85.2, C86.2, U12.2 (AREG)
unnamed: C90.1, C91.1, U12.24 (DREG)
unnamed: C88.2, U12.3 (VREF)
unnamed: C102.2, C103.2, U13.2 (AREG)
unnamed: C107.1, C108.1, U13.24 (DREG)
unnamed: C105.2, U13.3 (VREF)
unnamed: C119.2, C120.2, U14.2 (AREG)
unnamed: C124.1, C125.1, U14.24 (DREG)
unnamed: C122.2, U14.3 (VREF)
unnamed: C136.2, C137.2, U15.2 (AREG)
unnamed: C141.1, C142.1, U15.24 (DREG)
unnamed: C139.2, U15.3 (VREF)
unnamed: C153.2, C154.2, U16.2 (AREG)
unnamed: C158.1, C159.1, U16.24 (DREG)
unnamed: C156.2, U16.3 (VREF)
unnamed: C170.2, C171.2, U17.2 (AREG)
unnamed: C175.1, C176.1, U17.24 (DREG)
unnamed: C173.2, U17.3 (VREF)
